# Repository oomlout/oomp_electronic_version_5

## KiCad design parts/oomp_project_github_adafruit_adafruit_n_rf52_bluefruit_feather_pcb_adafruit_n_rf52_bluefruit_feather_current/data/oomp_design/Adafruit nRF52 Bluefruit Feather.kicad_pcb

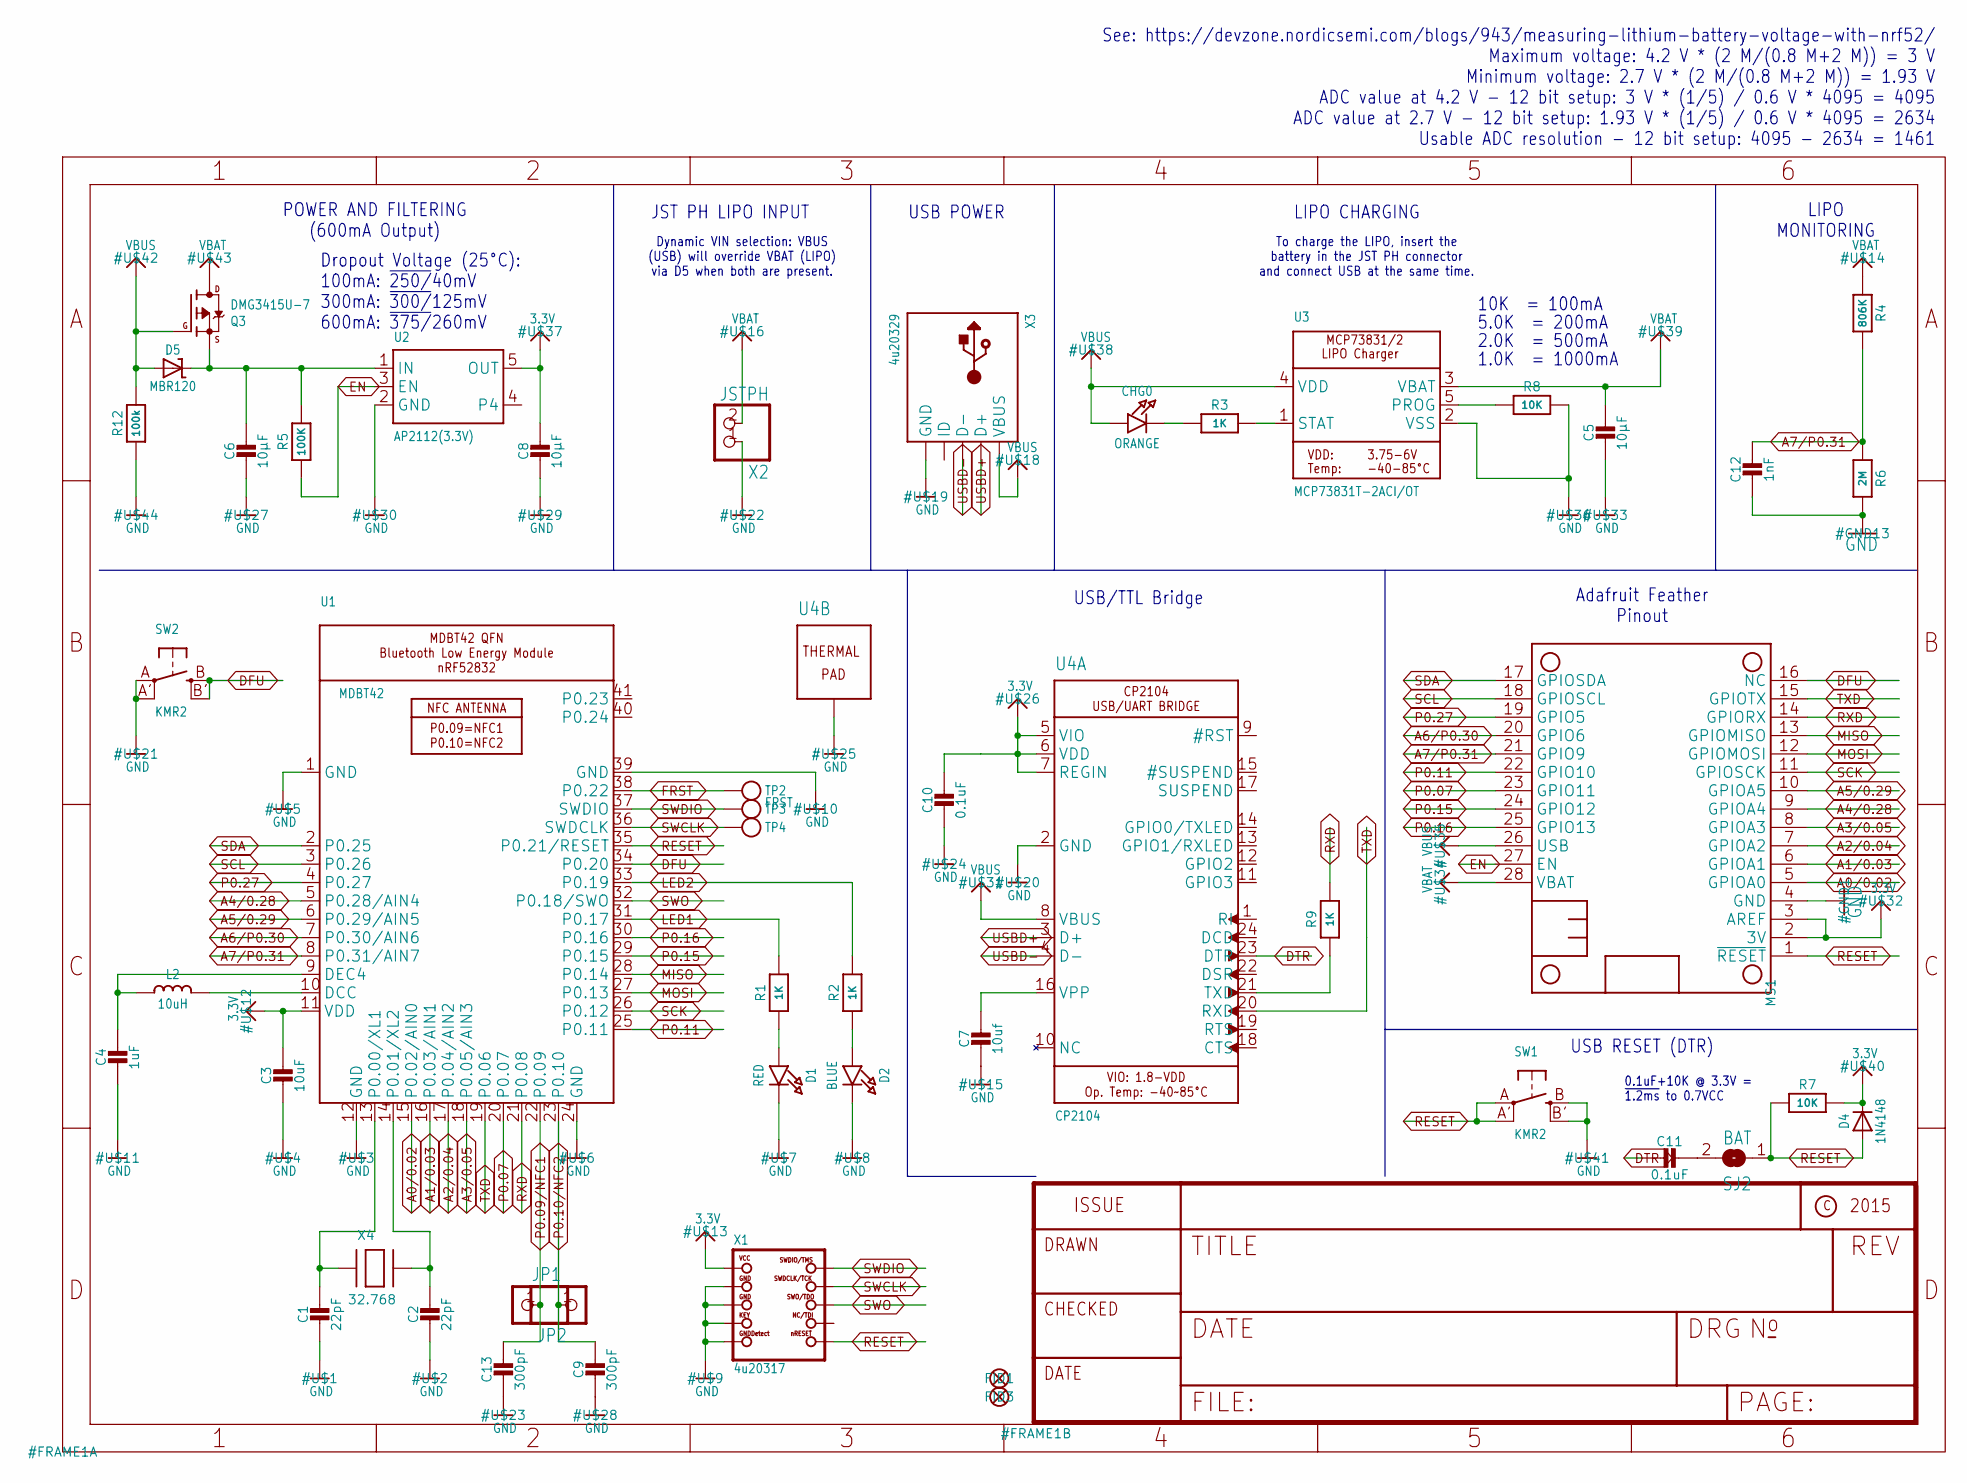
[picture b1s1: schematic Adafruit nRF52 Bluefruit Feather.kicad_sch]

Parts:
C1, C2: 22pF; 0603-NO
C3: 10uF; 0805-NO
C4: 1uF; 0603-NO
C5, C6, C8: 10µF; 0805-NO
C7: 10uf; 0805-NO
C9, C13: 300pF; _0603MP
C10, C11: 0.1uF; 0603-NO
C12: 1nF; 0603-NO
CHG0: ORANGE; CHIPLED_0805_NOOUTLINE
D1: RED; CHIPLED_0805_NOOUTLINE
D2: BLUE; CHIPLED_0805_NOOUTLINE
D4: 1N4148; SOD-323
D5: MBR120; SOD-123
FID1, FID3: FIDUCIAL_1MM
JP1, JP2: HEADER-1X12MM; 1X01_2MM
L2: 10uH; 0805-NO
MS1: FEATHERWING_NODIM
Q3: DMG3415U-7; SOT23-R
R1, R2, R3, R9: 1K; 0603-NO
R4: 806K; 0603-NO
R5: 100K; 0603-NO
R6: 2M; 0603-NO
R7, R8: 10K; 0603-NO
R12: 100k; 0603-NO
SJ2: BAT; SOLDERJUMPER_CLOSEDWIRE
SW1, SW2: KMR2; BTN_KMR2_4.6X2.8
TP2: FRST; PAD-1.5X2.0
TP3, TP4: TESTPOINTROUND2MM; TESTPOINT_ROUND_2MM
U1: MDBT42; BLE_MODULE_RAYTAC_MDBT42
U2: AP2112(3.3V); SOT23-5
U3: MCP73831T-2ACI/OT; SOT23-5
U4: CP2104; QFN24_4MM_SMSC
X1: 4u20317; 2X05_1.27MM_BOX_POSTS
X2: JSTPH; JSTPH2
X3: 4u20329; 4UCONN_20329_V2
X4: 32.768; XTAL3215

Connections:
3.3V: C3.1, C8.1, C10.1, D4.C, MS1.2 (3V), MS1.3 (AREF), R7.2, U1.11 (VDD), U2.5 (OUT), U4.5 (VIO), U4.6 (VDD), U4.7 (REGIN), X1.1 (VCC)
A0/0.02: MS1.5 (GPIOA0), U1.15 (P0.02/AIN0)
A1/0.03: MS1.6 (GPIOA1), U1.16 (P0.03/AIN1)
A2/0.04: MS1.7 (GPIOA2), U1.17 (P0.04/AIN2)
A3/0.05: MS1.8 (GPIOA3), U1.18 (P0.05/AIN3)
A4/0.28: MS1.9 (GPIOA4), U1.5 (P0.28/AIN4)
A5/0.29: MS1.10 (GPIOA5), U1.6 (P0.29/AIN5)
A6/P0.30: MS1.20 (GPIO6), U1.7 (P0.30/AIN6)
A7/P0.31: C12.1, MS1.21 (GPIO9), R4.2, R6.1, U1.8 (P0.31/AIN7)
DFU: MS1.16 (NC), SW2.B (S), SW2.B' (S1), U1.34 (P0.20)
DTR: C11.2, U4.23 (DTR)
EN: MS1.27 (EN), R5.1, U2.3 (EN)
FRST: TP2.P$1, U1.38 (P0.22)
GND: C1.2, C2.2, C3.2, C4.2, C5.2, C6.2, C7.2, C8.2, C9.2, C10.2, C12.2, C13.2, D1.C, D2.C, MS1.4 (GND), R6.2, R8.2, R12.1, SW1.B (S), SW1.B' (S1), SW2.A, SW2.A' (P1), U1.1 (GND), U1.12 (GND), U1.24 (GND), U1.39 (GND), U2.2 (GND), U3.2 (VSS), U4.2 (GND), U4.THERM (TP), X1.3 (GND), X1.5 (GND), X1.7 (KEY), X1.9 (GNDDETECT), X2.1, X3.BASE@1 (GND), X3.BASE@2 (GND), X3.GND, X3.SPRT@1 (GND), X3.SPRT@2 (GND), X3.SPRT@3 (GND), X3.SPRT@4 (GND)
LED1: R1.2, U1.31 (P0.17)
LED2: R2.2, U1.33 (P0.19)
MISO: MS1.13 (GPIOMISO), U1.28 (P0.14)
MOSI: MS1.12 (GPIOMOSI), U1.27 (P0.13)
unnamed: C1.1, U1.13 (P0.00/XL1), X4.P$1
unnamed: C2.1, U1.14 (P0.01/XL2), X4.P$2
unnamed: L2.2, U1.10 (DCC)
unnamed: CHG0.C, R3.1
unnamed: D1.A, R1.1
unnamed: D2.A, R2.1
unnamed: C4.1, L2.1, U1.9 (DEC4)
unnamed: R3.2, U3.1 (STAT)
unnamed: R8.1, U3.5 (PROG)
unnamed: R9.1, U4.21 (TXD)
unnamed: C11.1, SJ2.2
unnamed: C7.1, U4.16 (VPP)
P0.07: MS1.23 (GPIO11), U1.20 (P0.07)
P0.09/NFC1: C13.1, JP2.1, U1.22 (P0.09)
P0.10/NFC2: C9.1, JP1.1, U1.23 (P0.10)
P0.11: MS1.22 (GPIO10), U1.25 (P0.11)
P0.15: MS1.24 (GPIO12), U1.29 (P0.15)
P0.16: MS1.25 (GPIO13), U1.30 (P0.16)
P0.27: MS1.19 (GPIO5), U1.4 (P0.27)
RESET: D4.A, MS1.1 (~RESET), R7.1, SJ2.1, SW1.A, SW1.A' (P1), U1.35 (P0.21/RESET), X1.10 (NRESET)
RXD: MS1.14 (GPIORX), R9.2, U1.21 (P0.08)
SCK: MS1.11 (GPIOSCK), U1.26 (P0.12)
SCL: MS1.18 (GPIOSCL), U1.3 (P0.26)
SDA: MS1.17 (GPIOSDA), U1.2 (P0.25)
SWCLK: TP4.P$1, U1.36 (SWDCLK), X1.4 (SWDCLK)
SWDIO: TP3.P$1, U1.37 (SWDIO), X1.2 (SWDIO)
SWO: U1.32 (P0.18/SWO), X1.6 (SWO)
TXD: MS1.15 (GPIOTX), U1.19 (P0.06), U4.20 (RXD)
USBD+: U4.3 (D+), X3.D+
USBD-: U4.4 (D-), X3.D-
VBAT: C5.1, MS1.28 (VBAT), Q3.3 (D), R4.1, U3.3 (VBAT), X2.2
VBUS: CHG0.A, D5.A, MS1.26 (USB), Q3.1 (G), R12.2, U3.4 (VDD), U4.8 (VBUS), X3.VBUS
VIN: C6.1, D5.C, Q3.2 (S), R5.2, U2.1 (IN)

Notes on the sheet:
LIPO CHARGING
Dynamic VIN selection: VBUS (USB) will override VBAT (LIPO) via D5 when both are present.
See: https://devzone.nordicsemi.com/blogs/943/measuring-lithium-battery-voltage-with-nrf52/ Maximum voltage: 4.2 V * (2 M/(0.8 M+2 M)) = 3 V Minimum voltage: 2.7 V * (2 M/(0.8 M+2 M)) = 1.93 V ADC value at 4.2 V - 12 bit setup: 3 V * (1/5) / 0.6 V * 4095 = 4095 ADC value at 2.7 V - 12 bit setup: 1.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
Dropout Voltage (25°C): 100mA: ~{250/}40mV 300mA: ~{300/}125mV 600mA: ~{375/}260mV
USB RESET (DTR)
JST PH LIPO INPUT
USB/TTL Bridge
To charge the LIPO, insert the battery in the JST PH connector and connect USB at the same time.
USB POWER
5.0K = 200mA
10K = 100mA
0.1uF+10K @ 3.3V = ~{1.2ms} to 0.7VCC
Adafruit Feather Pinout
POWER AND FILTERING (600mA Output)
LIPO MONITORING
1.0K = 1000mA
2.0K = 500mA

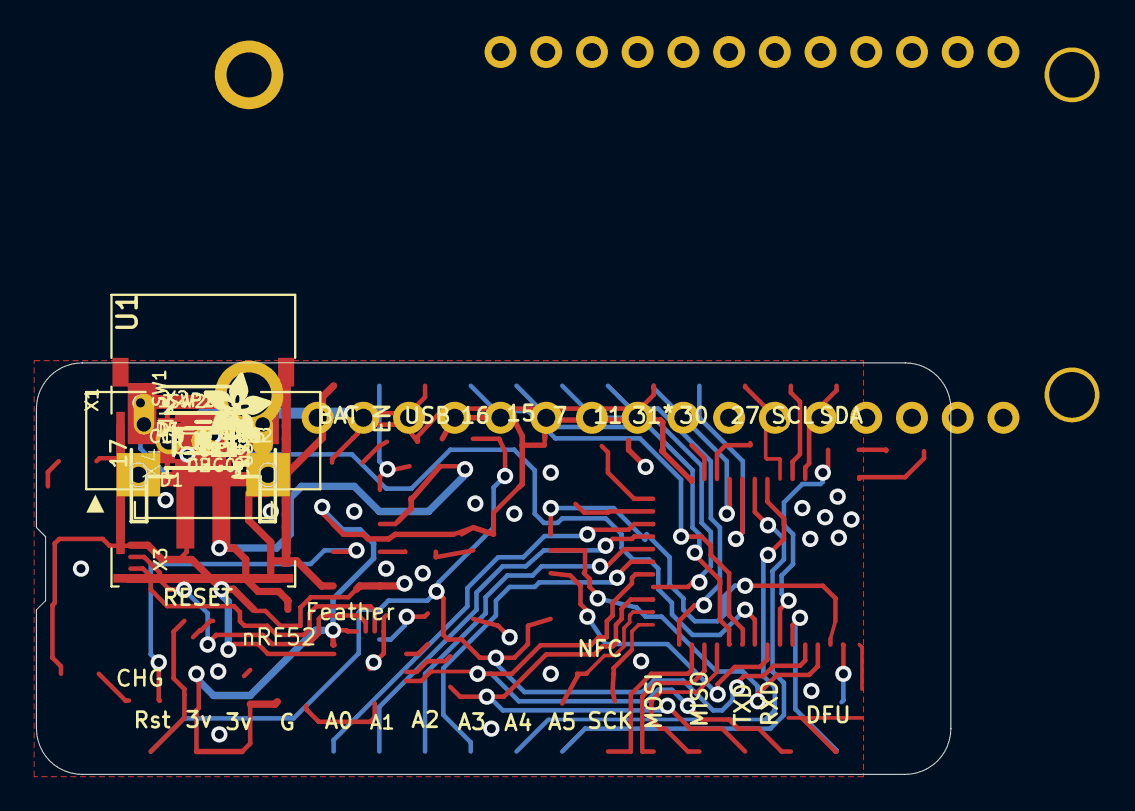
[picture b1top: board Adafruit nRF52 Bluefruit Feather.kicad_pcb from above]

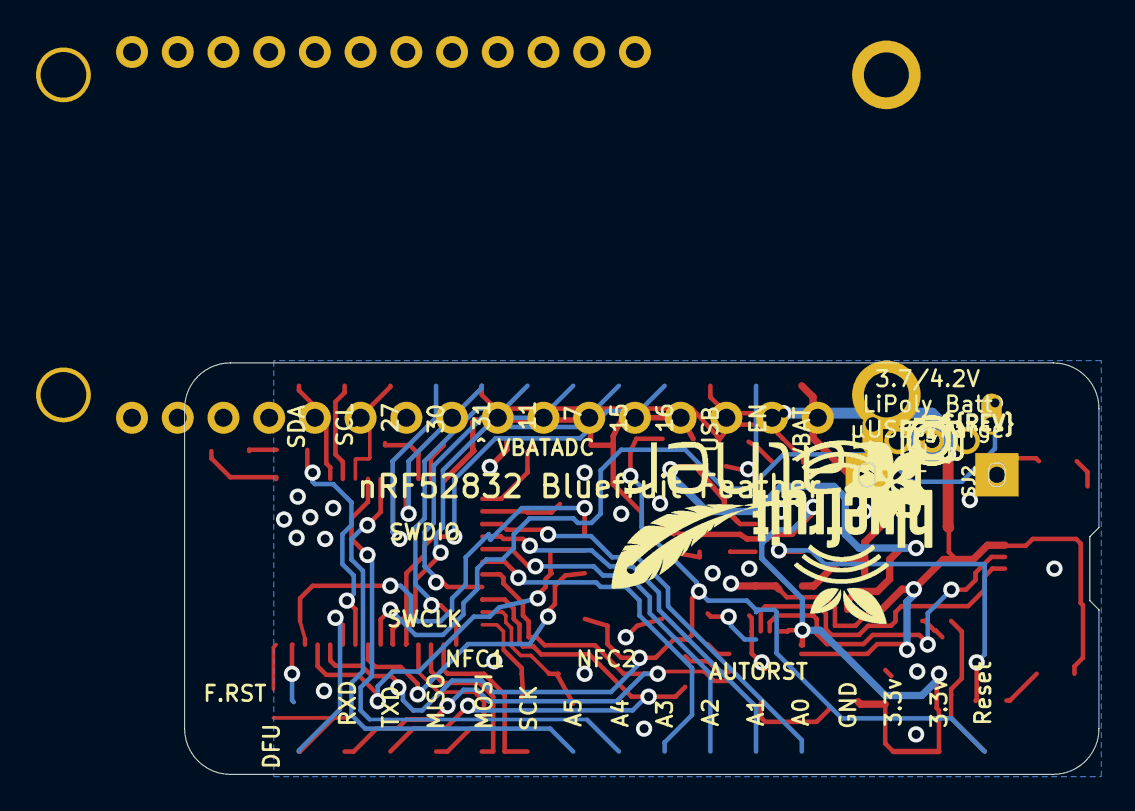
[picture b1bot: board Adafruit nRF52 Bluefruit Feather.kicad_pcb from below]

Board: 2 copper layers, 50.8 x 22.9 mm, 54 parts (8 on the bottom side), 51 nets.

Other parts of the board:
U$17: PCBFEAT-REV-040
U$45: BLUEFRUITLOGO_100MM
U$46: FEATHERLOGO_MED
U$47: ADAFRUIT_5MM
U$49: ADAFRUIT_3.5MM

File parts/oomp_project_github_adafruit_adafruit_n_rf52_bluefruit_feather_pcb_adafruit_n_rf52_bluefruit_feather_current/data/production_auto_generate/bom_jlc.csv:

Comment,Designator,Footprint,LCSC Part #
,"JP1,JP2",Adafruit nRF52 Bluefruit Feather-import-fps:1X01_2MM,C7501259
,U$49,Adafruit nRF52 Bluefruit Feather-import-fps:ADAFRUIT_3.5MM,
,U$47,Adafruit nRF52 Bluefruit Feather-import-fps:ADAFRUIT_5MM,
,U$45,Adafruit nRF52 Bluefruit Feather-import-fps:BLUEFRUITLOGO_100MM,
,U$46,Adafruit nRF52 Bluefruit Feather-import-fps:FEATHERLOGO_MED,
,U$17,Adafruit nRF52 Bluefruit Feather-import-fps:PCBFEAT-REV-040,
,"TP3,TP4",Adafruit nRF52 Bluefruit Feather-import-fps:TESTPOINT_ROUND_2MM,
0.1uF,"C10,C11",Adafruit nRF52 Bluefruit Feather-import-fps:0603-NO,C14663
100K,R5,Adafruit nRF52 Bluefruit Feather-import-fps:0603-NO,C25803
100k,R12,Adafruit nRF52 Bluefruit Feather-import-fps:0603-NO,C25803
10K,"R7,R8",Adafruit nRF52 Bluefruit Feather-import-fps:0603-NO,C98220
10uF,C3,Adafruit nRF52 Bluefruit Feather-import-fps:0805-NO,
10uf,C7,Adafruit nRF52 Bluefruit Feather-import-fps:0805-NO,
10uH,L2,Adafruit nRF52 Bluefruit Feather-import-fps:0805-NO,
10µF,"C5,C6,C8",Adafruit nRF52 Bluefruit Feather-import-fps:0805-NO,
1K,"R1,R2,R3,R9",Adafruit nRF52 Bluefruit Feather-import-fps:0603-NO,C2907002
1N4148,D4,Adafruit nRF52 Bluefruit Feather-import-fps:SOD-323,
1nF,C12,Adafruit nRF52 Bluefruit Feather-import-fps:0603-NO,
1uF,C4,Adafruit nRF52 Bluefruit Feather-import-fps:0603-NO,C5673
22pF,"C1,C2",Adafruit nRF52 Bluefruit Feather-import-fps:0603-NO,C105620
2M,R6,Adafruit nRF52 Bluefruit Feather-import-fps:0603-NO,
300pF,"C9,C13",Adafruit nRF52 Bluefruit Feather-import-fps:_0603MP,
32.768,X4,Adafruit nRF52 Bluefruit Feather-import-fps:XTAL3215,
4u20317,X1,Adafruit nRF52 Bluefruit Feather-import-fps:2X05_1.27MM_BOX_POSTS,
4u20329,X3,Adafruit nRF52 Bluefruit Feather-import-fps:4UCONN_20329_V2,
806K,R4,Adafruit nRF52 Bluefruit Feather-import-fps:0603-NO,
AP2112(3.3V),U2,Adafruit nRF52 Bluefruit Feather-import-fps:SOT23-5,
BLUE,D2,Adafruit nRF52 Bluefruit Feather-import-fps:CHIPLED_0805_NOOUTLINE,
CP2104,U4,Adafruit nRF52 Bluefruit Feather-import-fps:QFN24_4MM_SMSC,
DMG3415U-7,Q3,Adafruit nRF52 Bluefruit Feather-import-fps:SOT23-R,
FEATHERWING_NODIM,MS1,Adafruit nRF52 Bluefruit Feather-import-fps:FEATHERWING_NODIM,
FRST,TP2,Adafruit nRF52 Bluefruit Feather-import-fps:PAD-1.5X2.0,
JSTPH,X2,Adafruit nRF52 Bluefruit Feather-import-fps:JSTPH2,
KMR2,"SW1,SW2",Adafruit nRF52 Bluefruit Feather-import-fps:BTN_KMR2_4.6X2.8,
MBR120,D5,Adafruit nRF52 Bluefruit Feather-import-fps:SOD-123,
MCP73831T-2ACI/OT,U3,Adafruit nRF52 Bluefruit Feather-import-fps:SOT23-5,
MDBT42,U1,Adafruit nRF52 Bluefruit Feather-import-fps:BLE_MODULE_RAYTAC_MDBT42,
ORANGE,CHG0,Adafruit nRF52 Bluefruit Feather-import-fps:CHIPLED_0805_NOOUTLINE,
RED,D1,Adafruit nRF52 Bluefruit Feather-import-fps:CHIPLED_0805_NOOUTLINE,

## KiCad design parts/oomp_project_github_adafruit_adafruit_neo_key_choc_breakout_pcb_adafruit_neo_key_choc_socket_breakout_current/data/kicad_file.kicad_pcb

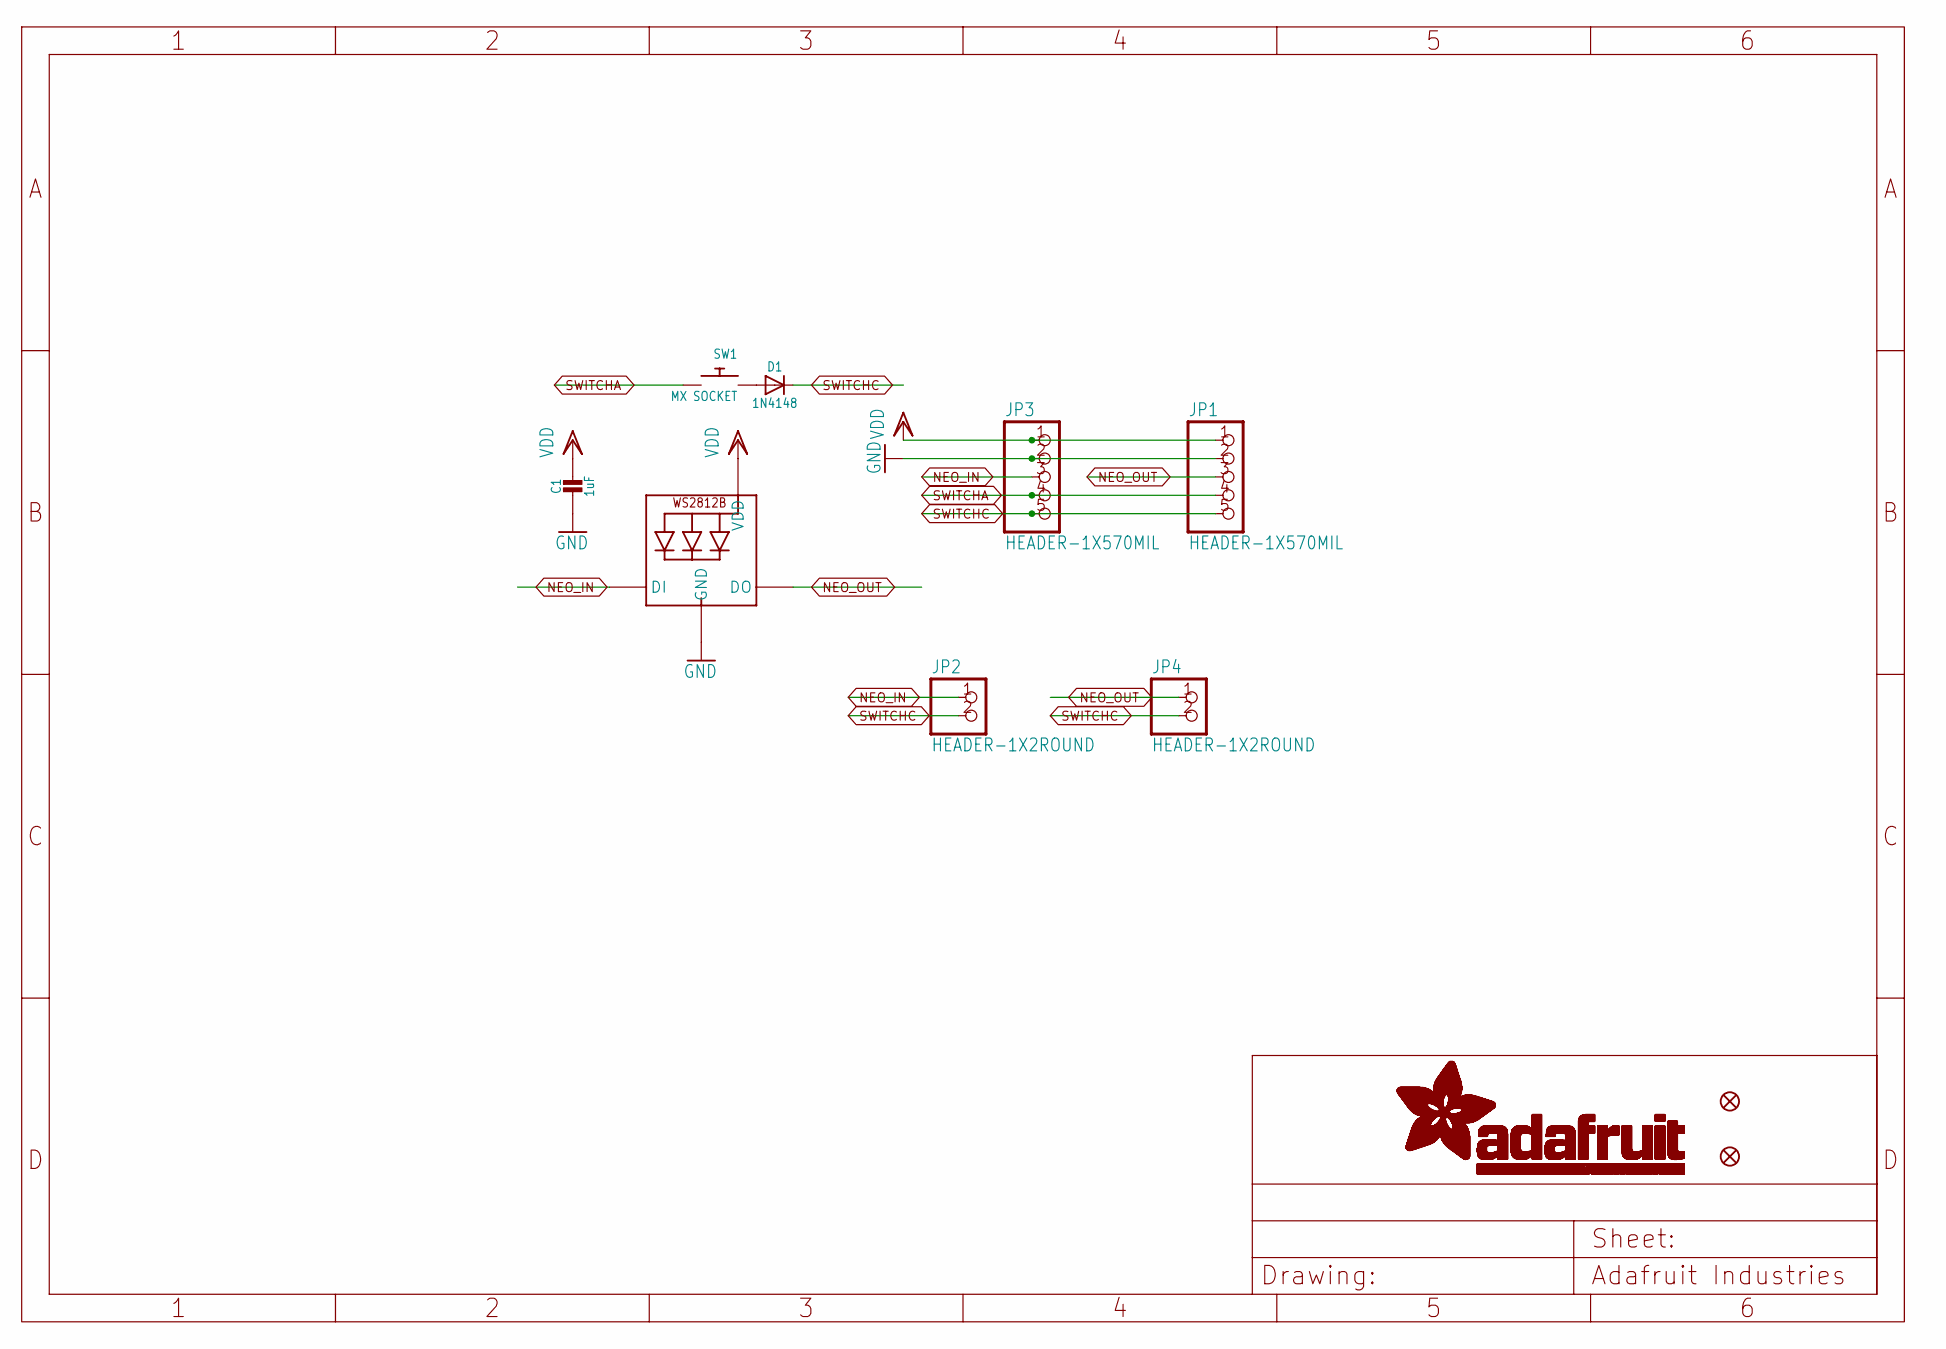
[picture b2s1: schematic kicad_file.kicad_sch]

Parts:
C1: 1uF; 0603-NO
D1: 1N4148; SOD-323
FID3, FID4: FIDUCIAL_1MM
JP1, JP3: HEADER-1X570MIL; 1X05_ROUND_70
JP2, JP4: HEADER-1X2ROUND; 1X02_ROUND
LED1: WS2812B_SK6812E; NEO3535_REVERSE
SW1: MX SOCKET; KAILH_CHOC_SOCKET

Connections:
GND: C1.2, JP1.2, JP3.2, LED1.3-GND (GND)
unnamed: D1.A, SW1.1
NEO_IN: JP2.1, JP3.3, LED1.4-DIN (DI)
NEO_OUT: JP1.3, JP4.1, LED1.2-DOUT (DO)
SWITCHA: JP1.4, JP3.4, SW1.2
SWITCHC: D1.C, JP1.5, JP2.2, JP3.5, JP4.2
VDD: C1.1, JP1.1, JP3.1, LED1.1-VDD (VDD)

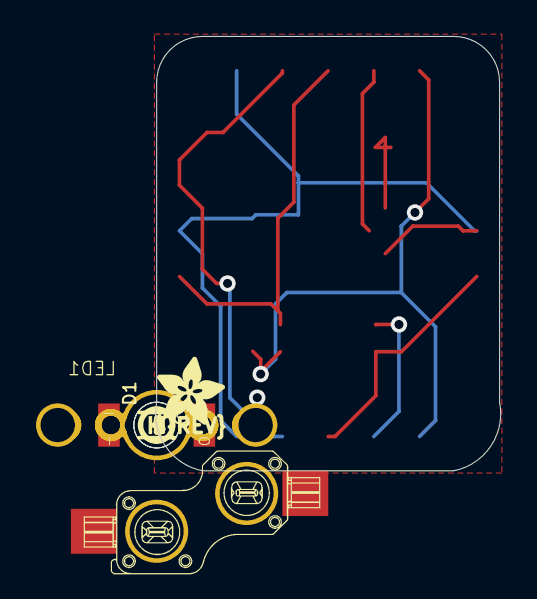
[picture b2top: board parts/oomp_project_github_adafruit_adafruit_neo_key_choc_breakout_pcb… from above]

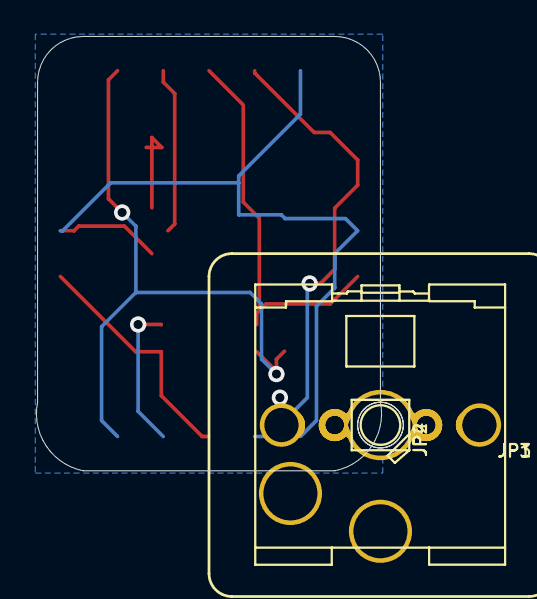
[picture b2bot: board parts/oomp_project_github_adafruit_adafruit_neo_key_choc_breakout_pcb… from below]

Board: 2 copper layers, 19.2 x 24.1 mm, 39 parts (16 on the bottom side), 7 nets.

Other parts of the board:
PLABEL0, PLABEL20: PLABEL0
PLABEL1: PLABEL1
PLABEL2: PLABEL2
PLABEL3: PLABEL3
PLABEL4: PLABEL4
PLABEL5: PLABEL5
PLABEL6, PLABEL21: PLABEL6
PLABEL7: PLABEL7
PLABEL8, PLABEL22: PLABEL8
PLABEL9, PLABEL23: PLABEL9
PLABEL10: PLABEL10
PLABEL11: PLABEL11
PLABEL12: PLABEL12
PLABEL13: PLABEL13
PLABEL14: PLABEL14
PLABEL15: PLABEL15
PLABEL16: PLABEL16
PLABEL17: PLABEL17
PLABEL18: PLABEL18
PLABEL19: PLABEL19
PLABEL200: PLABEL200
U$1: PCBFEAT-REV-040
U$2: ADAFRUIT_3.5MM
UNK_HOLE_0: dummyfp0
UNK_HOLE_1: dummyfp1

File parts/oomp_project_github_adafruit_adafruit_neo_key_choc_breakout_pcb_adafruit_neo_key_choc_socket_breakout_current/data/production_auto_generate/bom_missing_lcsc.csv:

Designator,Comment,Footprint,OOMP ID,Reason
D1,1N4148,Adafruit NeoKey CHOC Socket Breakout-import-fps:SOD-323,electronic_diode_switching_sod_323_onsemi_1n4148ws,No verified LCSC part number
LED1,WS2812B_SK6812E,Adafruit NeoKey CHOC Socket Breakout-import-fps:NEO3535_REVERSE,,No verified LCSC part number
PLABEL0,,Adafruit NeoKey CHOC Socket Breakout-import-fps:PLABEL0,,No verified LCSC part number
PLABEL1,,Adafruit NeoKey CHOC Socket Breakout-import-fps:PLABEL1,,No verified LCSC part number
PLABEL2,,Adafruit NeoKey CHOC Socket Breakout-import-fps:PLABEL2,,No verified LCSC part number
PLABEL3,,Adafruit NeoKey CHOC Socket Breakout-import-fps:PLABEL3,,No verified LCSC part number
PLABEL4,,Adafruit NeoKey CHOC Socket Breakout-import-fps:PLABEL4,,No verified LCSC part number
PLABEL5,,Adafruit NeoKey CHOC Socket Breakout-import-fps:PLABEL5,,No verified LCSC part number
PLABEL6,,Adafruit NeoKey CHOC Socket Breakout-import-fps:PLABEL6,,No verified LCSC part number
PLABEL7,,Adafruit NeoKey CHOC Socket Breakout-import-fps:PLABEL7,,No verified LCSC part number
PLABEL8,,Adafruit NeoKey CHOC Socket Breakout-import-fps:PLABEL8,,No verified LCSC part number
PLABEL9,,Adafruit NeoKey CHOC Socket Breakout-import-fps:PLABEL9,,No verified LCSC part number
PLABEL10,,Adafruit NeoKey CHOC Socket Breakout-import-fps:PLABEL10,,No verified LCSC part number
PLABEL11,,Adafruit NeoKey CHOC Socket Breakout-import-fps:PLABEL11,,No verified LCSC part number
PLABEL12,,Adafruit NeoKey CHOC Socket Breakout-import-fps:PLABEL12,,No verified LCSC part number
PLABEL13,,Adafruit NeoKey CHOC Socket Breakout-import-fps:PLABEL13,,No verified LCSC part number
PLABEL14,,Adafruit NeoKey CHOC Socket Breakout-import-fps:PLABEL14,,No verified LCSC part number
PLABEL15,,Adafruit NeoKey CHOC Socket Breakout-import-fps:PLABEL15,,No verified LCSC part number
PLABEL16,,Adafruit NeoKey CHOC Socket Breakout-import-fps:PLABEL16,,No verified LCSC part number
PLABEL17,,Adafruit NeoKey CHOC Socket Breakout-import-fps:PLABEL17,,No verified LCSC part number
PLABEL18,,Adafruit NeoKey CHOC Socket Breakout-import-fps:PLABEL18,,No verified LCSC part number
PLABEL19,,Adafruit NeoKey CHOC Socket Breakout-import-fps:PLABEL19,,No verified LCSC part number
PLABEL20,,Adafruit NeoKey CHOC Socket Breakout-import-fps:PLABEL0,,No verified LCSC part number
PLABEL21,,Adafruit NeoKey CHOC Socket Breakout-import-fps:PLABEL6,,No verified LCSC part number
PLABEL22,,Adafruit NeoKey CHOC Socket Breakout-import-fps:PLABEL8,,No verified LCSC part number
PLABEL23,,Adafruit NeoKey CHOC Socket Breakout-import-fps:PLABEL9,,No verified LCSC part number
PLABEL200,,Adafruit NeoKey CHOC Socket Breakout-import-fps:PLABEL200,,No verified LCSC part number
SW1,MX SOCKET,Adafruit NeoKey CHOC Socket Breakout-import-fps:KAILH_CHOC_SOCKET,,No verified LCSC part number
U$1,,Adafruit NeoKey CHOC Socket Breakout-import-fps:PCBFEAT-REV-040,,No verified LCSC part number
U$2,,Adafruit NeoKey CHOC Socket Breakout-import-fps:ADAFRUIT_3.5MM,,No verified LCSC part number
